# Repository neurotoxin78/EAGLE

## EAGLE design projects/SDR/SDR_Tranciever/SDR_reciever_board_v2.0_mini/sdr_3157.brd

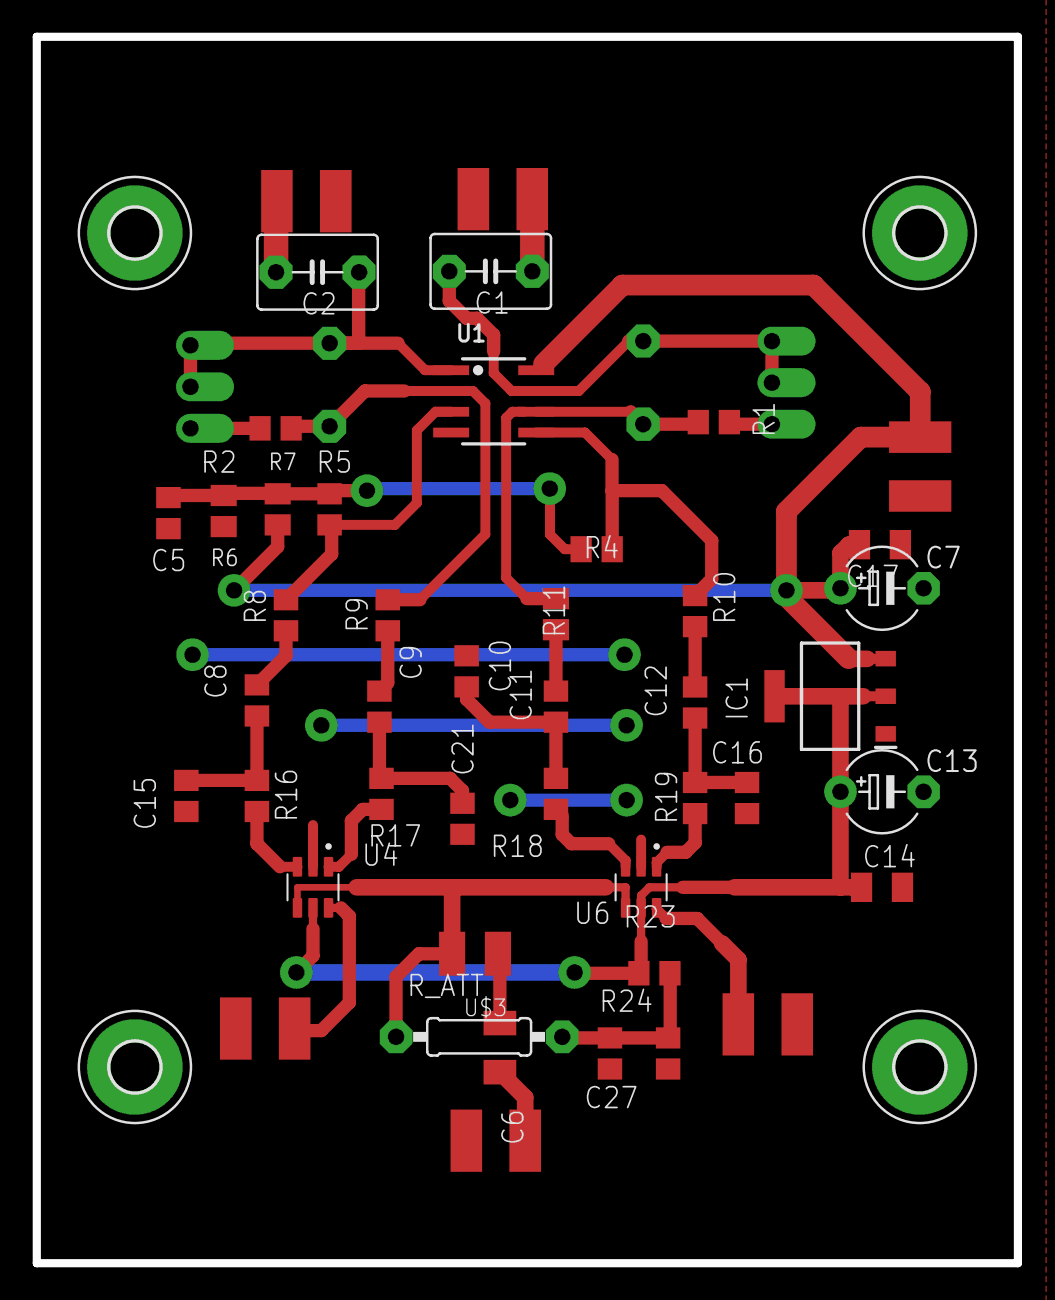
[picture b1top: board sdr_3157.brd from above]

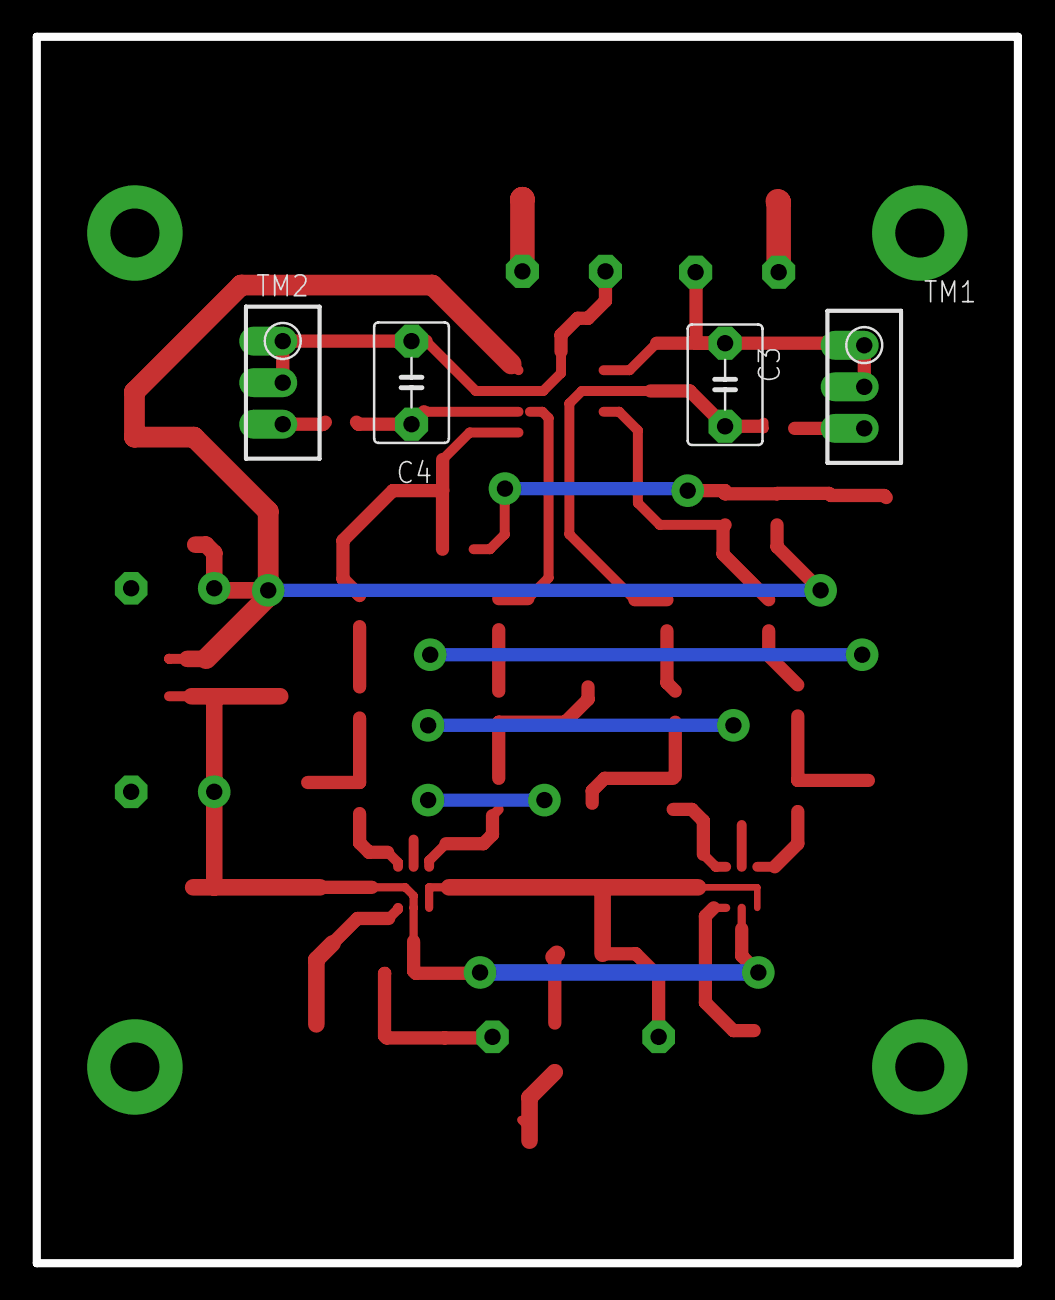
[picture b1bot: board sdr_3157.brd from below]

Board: 2 copper layers, 60.0 x 75.0 mm, 53 parts (4 on the bottom side), 32 nets.

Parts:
C1, C2: 1uF; C050-045X075
C3, C4: 200pF; C050-045X075
C5: 10uF; C0805
C6: 22nF; C1206K
C7, C13: E5-5
C8, C9, C11, C12, C27: 1uF; C0805
C10, C15, C16, C21: 22nF; C0805
C14, C17: C0805
COS: 2XSMD_PIN
H1, H2, H3, H4: MOUNT-PAD-ROUND3.0; 3,0-PAD
I: 2XSMD_PIN
IC1: LM1117-33; SOT230P700X180-4N
Q: 2XSMD_PIN
R1, R2: 7k5; R0805
R4: 10k; M0805
R5: 10k; R0805
R6, R7, R11: 1k; M0805
R8, R9, R10, R23, R24: 1k; R0805
R16, R17, R18, R19: 20; R0805
RF_IN, RF_IN1: 2XSMD_PIN
R_ATT: 20; R1210
SIN: 2XSMD_PIN
TM1, TM2: 5k; RTRIM3296W
U1: NE5532D; SO08
U4, U6: SN74LVC1G3157DBVR; SOT95P280X145-6N
U$3: 100uH; 0207/10

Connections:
12V: C7.+, C17.2, IC1.3, R7.1, RF_IN1.P$2, U1.8
ANTENNA: R_ATT.2, U4.4, U6.4, U$3.2
COS_IN: COS.P$2, U4.6
GND: C5.1, C7.-, C10.2, C13.-, C14.2, C15.2, C16.1, C17.1, C21.1, C27.1, COS.P$1, H1.B3,0, H2.B3,0, H3.B3,0, H4.B3,0, I.P$1, IC1.1, Q.P$2, R6.1, R23.1, RF_IN.P$1, RF_IN1.P$1, SIN.P$1, U1.4, U4.2, U6.2
unnamed: C6.2, RF_IN.P$2
unnamed: C6.1, R_ATT.1
unnamed: R16.1, U4.3
unnamed: R17.1, U4.1
unnamed: R18.1, U6.3
unnamed: R19.1, U6.1
unnamed: C8.1, C15.1, R16.2
unnamed: C9.1, C21.2, R17.2
unnamed: C10.1, C11.1, R18.2
unnamed: C12.1, C16.2, R19.2
unnamed: C8.2, R8.1
unnamed: C9.2, R9.1
unnamed: C11.2, R11.1
unnamed: C12.2, R10.1
unnamed: R5.2, R8.2, U1.3
unnamed: C3.1, R2.1, R9.2, U1.2
unnamed: R4.2, R10.2, U1.5
unnamed: C4.1, R1.1, R11.2, U1.6
unnamed: C5.2, R4.1, R5.1, R6.2, R7.2
unnamed: C2.1, C3.2, TM1.1, TM1.2, U1.1
unnamed: C2.2, Q.P$1
unnamed: C1.1, I.P$2
unnamed: C1.2, C4.2, TM2.1, TM2.2, U1.7
unnamed: C27.2, R23.2, R24.2, U$3.1
unnamed: R2.2, TM1.3
unnamed: R1.2, TM2.3
SIN_IN: SIN.P$2, U6.6
VCC: C13.+, C14.1, IC1.2, IC1.4, R24.1, U4.5, U6.5

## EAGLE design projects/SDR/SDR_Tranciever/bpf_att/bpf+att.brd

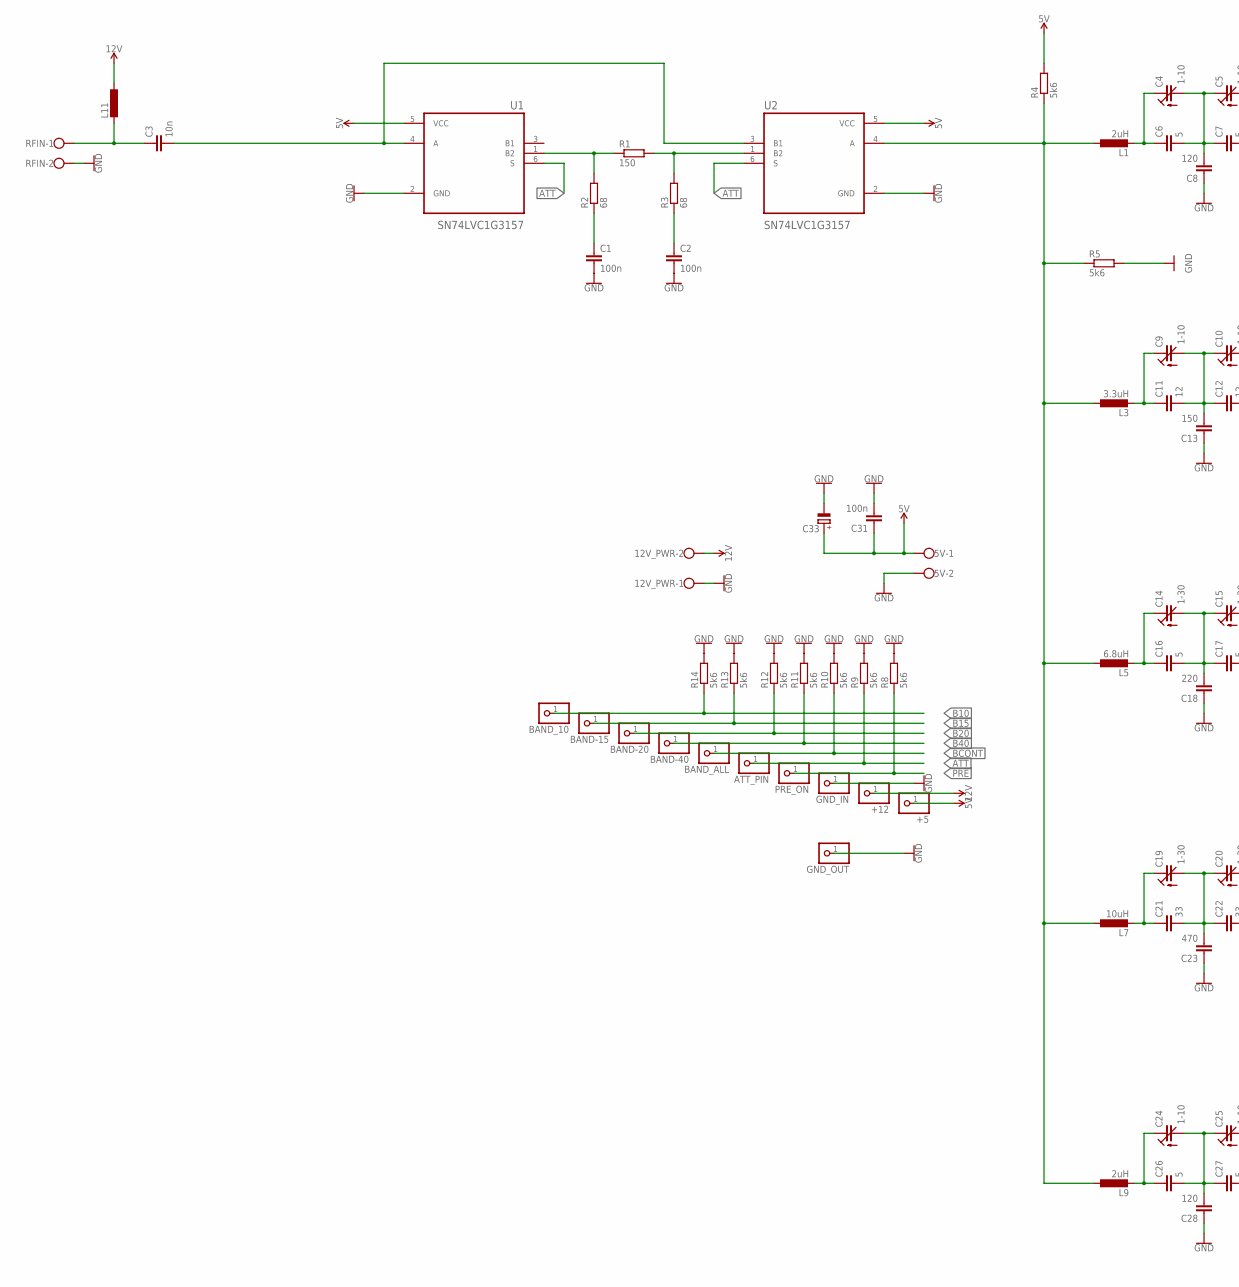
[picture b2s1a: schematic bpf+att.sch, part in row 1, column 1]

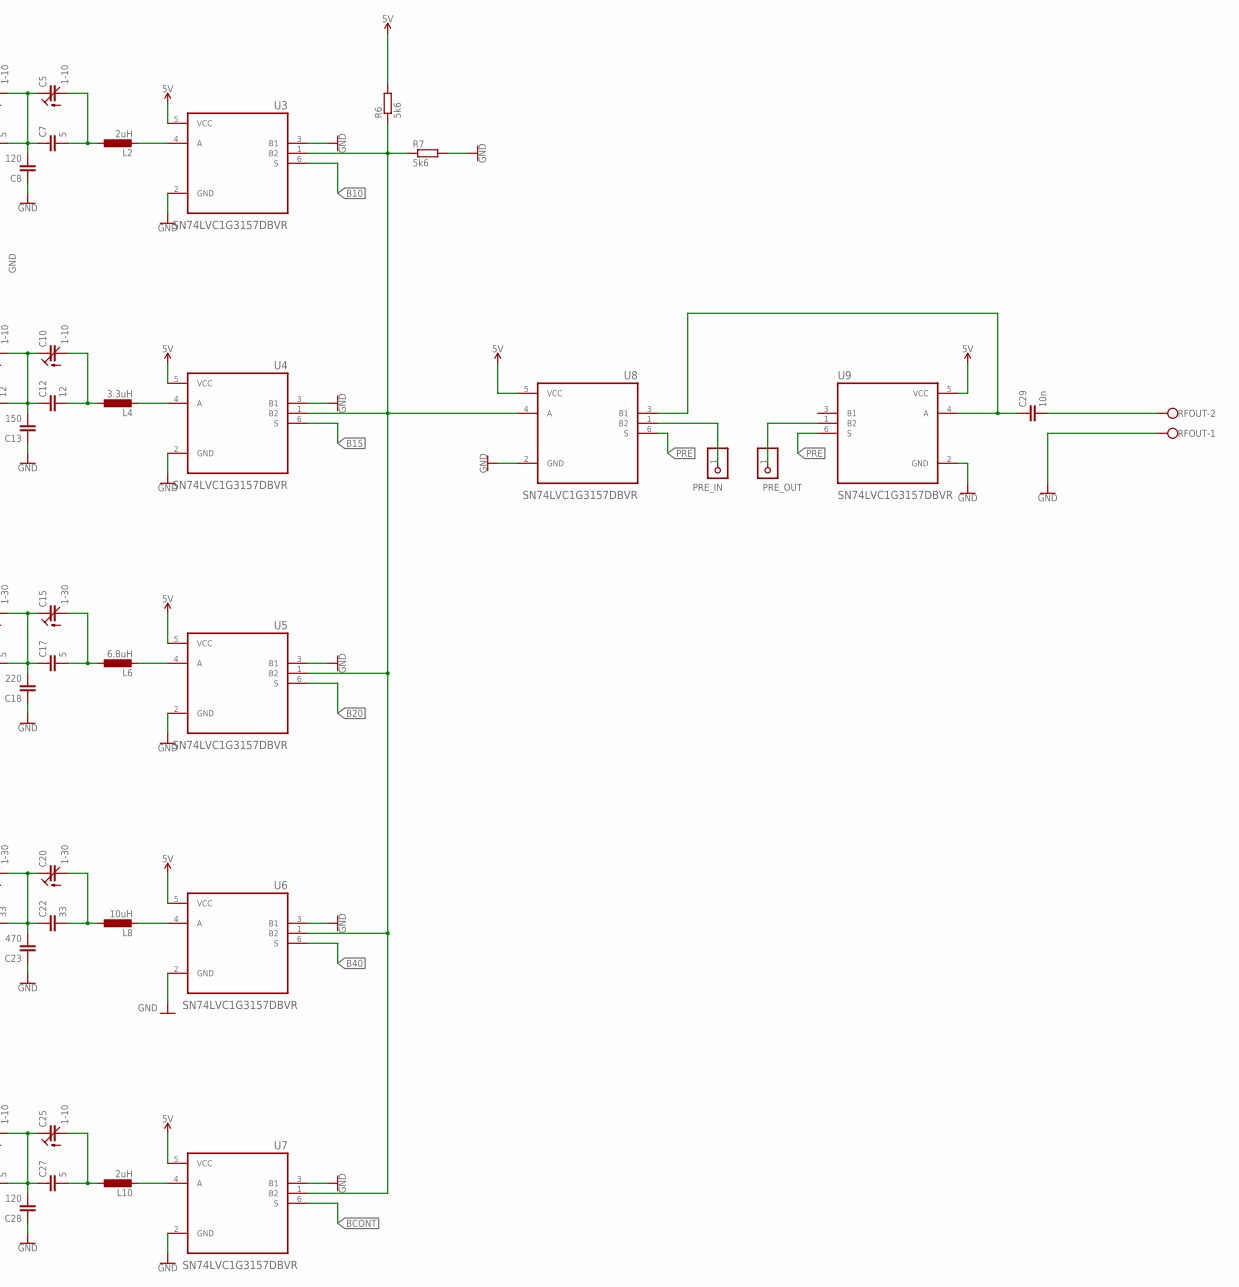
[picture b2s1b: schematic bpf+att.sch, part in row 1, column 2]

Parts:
5V, 12V_PWR: W237-102
+5, +12: PINHD-1X1; 1X01
ATT_PIN: PINHD-1X1; 1X01
BAND-15, BAND-20, BAND-40: PINHD-1X1; 1X01
BAND_10: PINHD-1X1; 1X01
BAND_ALL: PINHD-1X1; 1X01
C1, C2, C31: 100n; C1206
C3, C29: 10n; C1206K
C4, C5, C9, C10, C24, C25: 1-10; CTRIM3050.504
C6, C7, C16, C17, C26, C27: 5; C1206K
C8, C28: 120; C1206K
C11, C12: 12; C1206K
C13: 150; C1206K
C14, C15, C19, C20: 1-30; CTRIM3050.504
C18: 220; C1206K
C21, C22: 33; C1206K
C23: 470; C1206K
C33: CPOL-EUSMCD; SMC_D
GND_IN: PINHD-1X1; 1X01
GND_OUT: PINHD-1X1; 1X01
L1, L2, L9, L10: 2uH; 0204/7
L3, L4: 3.3uH; 0204/7
L5, L6: 6.8uH; 0204/7
L7, L8: 10uH; 0204/7
L11: L-EU0204/7; 0204/7
PRE_IN: PINHD-1X1; 1X01
PRE_ON: PINHD-1X1; 1X01
PRE_OUT: PINHD-1X1; 1X01
R1: 150; R1206
R2, R3: 68; R1206
R4, R5, R8, R9: 5k6; R1206
R6, R7, R10, R11, R12, R13, R14: 5k6; R0805
RFIN: W237-102
RFOUT: W237-102
U1, U2: SN74LVC1G3157; SOT95P280X145-6N
U3, U4, U5, U6, U7, U8, U9: SN74LVC1G3157DBVR; SOT95P280X145-6N

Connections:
5V: 5V.1, +5.1, C31.1, C33.+, R4.2, R6.2, U1.5 (VCC), U2.5 (VCC), U3.5 (VCC), U4.5 (VCC), U5.5 (VCC), U6.5 (VCC), U7.5 (VCC), U8.5 (VCC), U9.5 (VCC)
12V: 12V_PWR.2, +12.1, L11.1
ATT: ATT_PIN.1, R9.1, U1.6 (S), U2.6 (S)
B10: BAND_10.1, R14.1, U3.6 (S)
B15: BAND-15.1, R13.1, U4.6 (S)
B20: BAND-20.1, R12.1, U5.6 (S)
B40: BAND-40.1, R11.1, U6.6 (S)
BCONT: BAND_ALL.1, R10.1, U7.6 (S)
BYPASS: R6.1, R7.1, U3.1 (B2), U4.1 (B2), U5.1 (B2), U6.1 (B2), U7.1 (B2), U8.4 (A)
FILTER_INPUT: L1.1, L3.1, L5.1, L7.1, L9.1, R4.1, R5.1, U2.4 (A)
GND: 5V.2, 12V_PWR.1, C1.2, C2.2, C8.1, C13.1, C18.1, C23.1, C28.1, C31.2, C33.-, GND_IN.1, GND_OUT.1, R5.2, R7.2, R8.2, R9.2, R10.2, R11.2, R12.2, R13.2, R14.2, RFIN.2, RFOUT.1, U1.2 (GND), U2.2 (GND), U3.2 (GND), U3.3 (B1), U4.2 (GND), U4.3 (B1), U5.2 (GND), U5.3 (B1), U6.2 (GND), U6.3 (B1), U7.2 (GND), U7.3 (B1), U8.2 (GND), U9.2 (GND)
unnamed: R1.1, R2.2, U1.1 (B2)
unnamed: R1.2, R3.2, U2.1 (B2)
unnamed: C1.1, R2.1
unnamed: C2.1, R3.1
unnamed: C3.2, U1.4 (A), U2.3 (B1)
unnamed: C3.1, L11.2, RFIN.1
unnamed: C4.1 (E), C6.1, L1.2
unnamed: C4.2 (A), C5.1 (E), C6.2, C7.1, C8.2
unnamed: C5.2 (A), C7.2, L2.1
unnamed: L2.2, U3.4 (A)
unnamed: C29.1, U8.3 (B1), U9.4 (A)
unnamed: C9.1 (E), C11.1, L3.2
unnamed: C9.2 (A), C10.1 (E), C11.2, C12.1, C13.2
unnamed: C10.2 (A), C12.2, L4.1
unnamed: L4.2, U4.4 (A)
unnamed: C29.2, RFOUT.2
unnamed: PRE_IN.1, U8.1 (B2)
unnamed: C14.1 (E), C16.1, L5.2
unnamed: C14.2 (A), C15.1 (E), C16.2, C17.1, C18.2
unnamed: C15.2 (A), C17.2, L6.1
unnamed: L6.2, U5.4 (A)
unnamed: PRE_OUT.1, U9.1 (B2)
unnamed: C19.1 (E), C21.1, L7.2
unnamed: C19.2 (A), C20.1 (E), C21.2, C22.1, C23.2
unnamed: C20.2 (A), C22.2, L8.1
unnamed: L8.2, U6.4 (A)
unnamed: C24.1 (E), C26.1, L9.2
unnamed: C24.2 (A), C25.1 (E), C26.2, C27.1, C28.2
unnamed: C25.2 (A), C27.2, L10.1
unnamed: L10.2, U7.4 (A)
PRE: PRE_ON.1, R8.1, U8.6 (S), U9.6 (S)

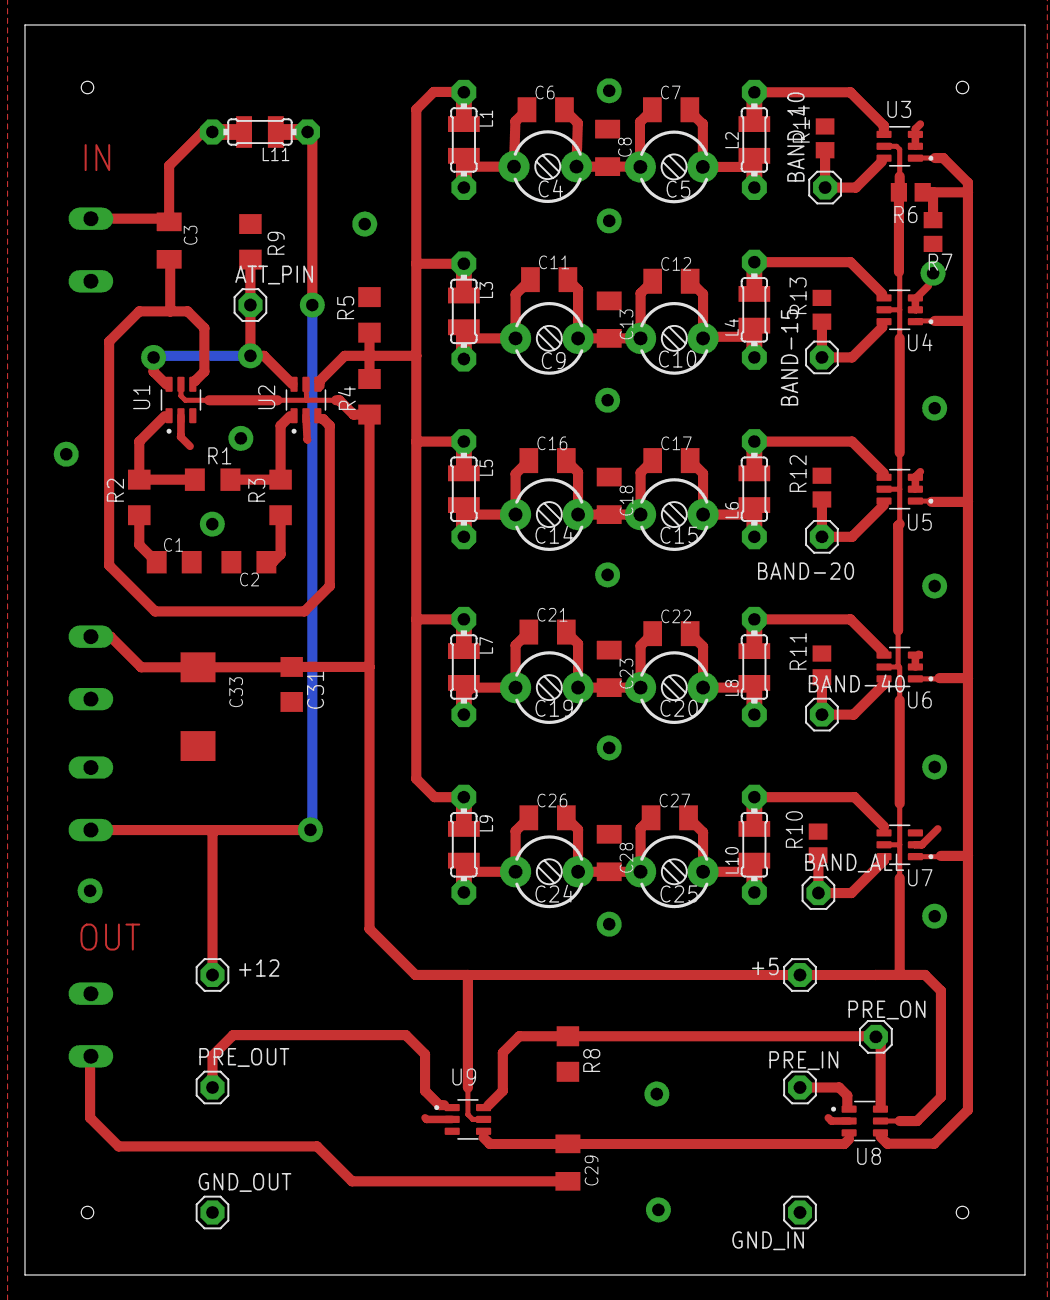
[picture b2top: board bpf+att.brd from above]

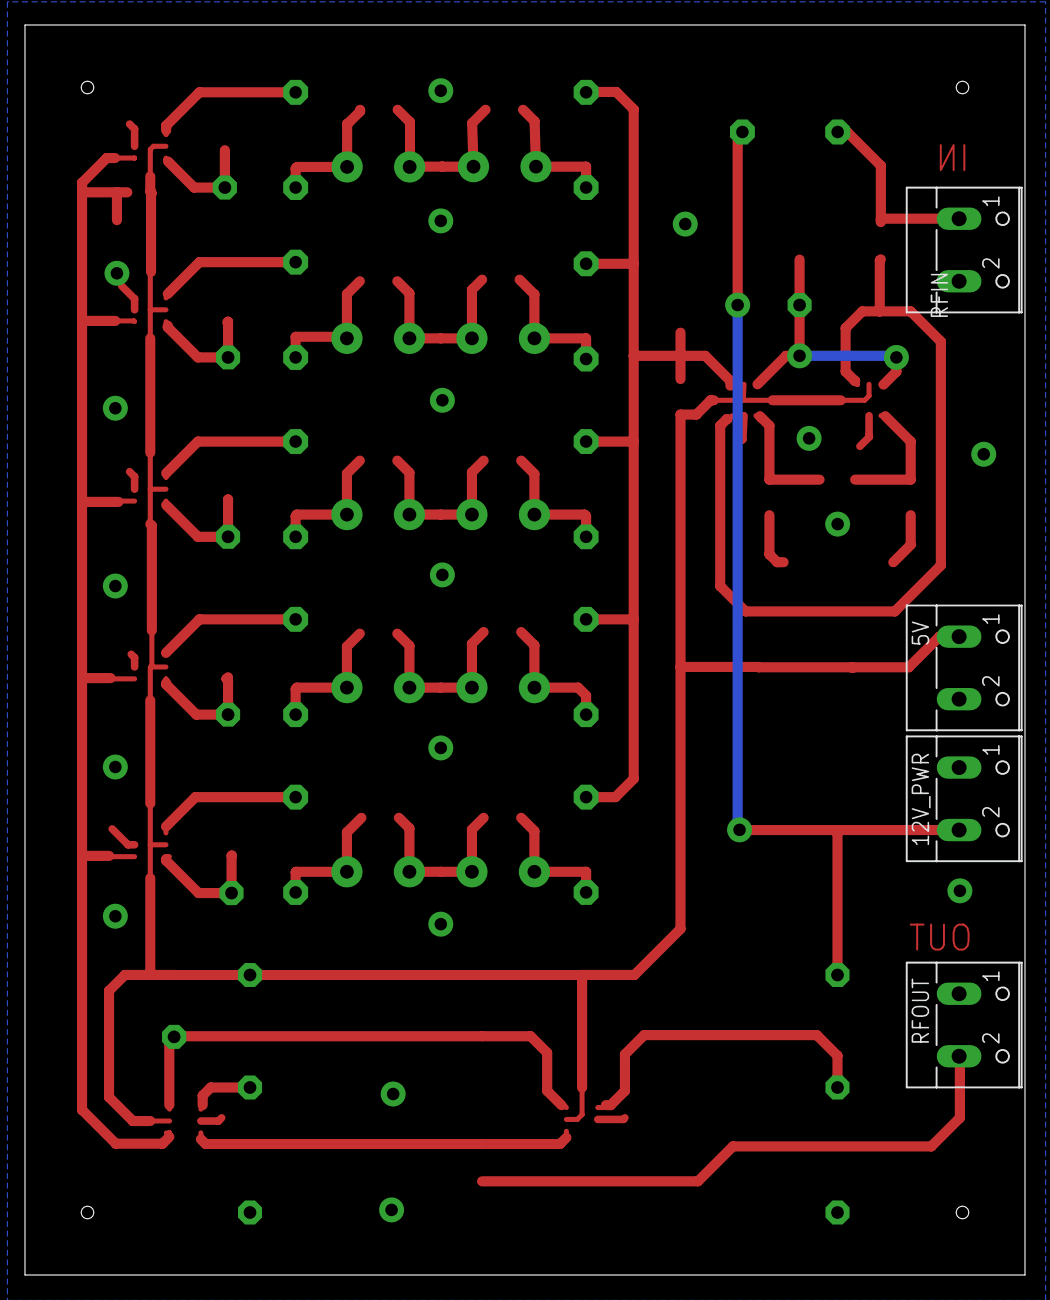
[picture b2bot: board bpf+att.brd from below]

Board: 2 copper layers, 80.0 x 100.0 mm, 82 parts (4 on the bottom side), 42 nets.

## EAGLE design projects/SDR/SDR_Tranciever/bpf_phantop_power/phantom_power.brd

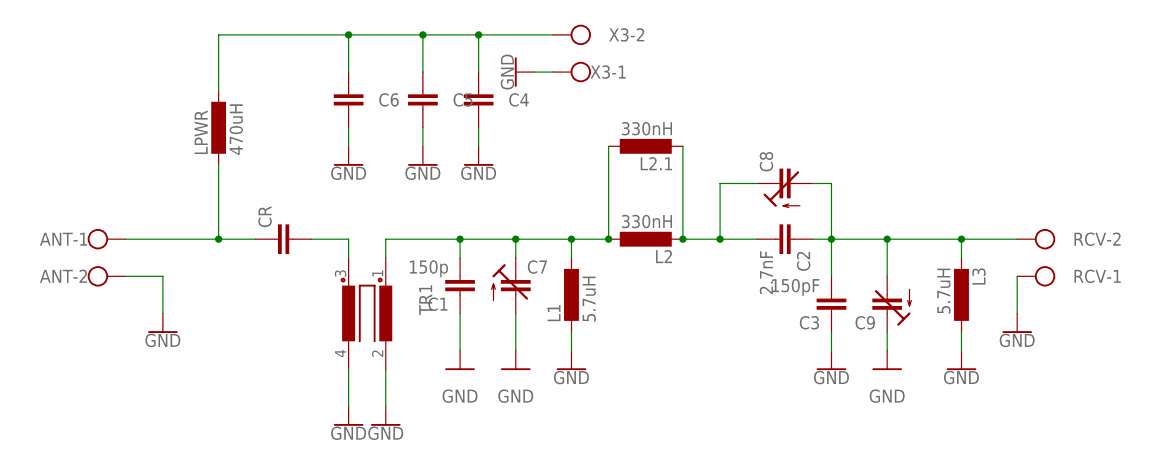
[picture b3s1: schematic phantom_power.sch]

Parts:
ANT: W237-102
C1: 150p; C1206K
C2: 2.7nF; C1206K
C3: 150pF; C1206K
C4, C5, C6: C-EUC1206K; C1206K
C7, C8, C9: C-TRIMM3050.504; CTRIM3050.504
CR: C-EUC1206K; C1206K
L1, L3: 5.7uH; 0204/7
L2: 330nH; L1812
L2.1: 330nH; 0204/7
LPWR: 470uH; 0204/7
RCV: W237-102
TR1: R1405UB1/2; B1/2
X3: W237-102

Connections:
GND: ANT.2, C1.1, C3.1, C4.2, C5.2, C6.2, C7.2 (A), C9.1 (E), L1.2, L3.1, RCV.1, TR1.2, TR1.4, X3.1
unnamed: ANT.1, CR.1, LPWR.2
unnamed: C4.1, C5.1, C6.1, LPWR.1, X3.2
unnamed: C2.1, C3.2, C8.2 (A), C9.2 (A), L3.2, RCV.2
unnamed: C1.2, C7.1 (E), L1.1, L2.1, L2.1.1, TR1.1
unnamed: C2.2, C8.1 (E), L2.2, L2.1.2
unnamed: CR.2, TR1.3

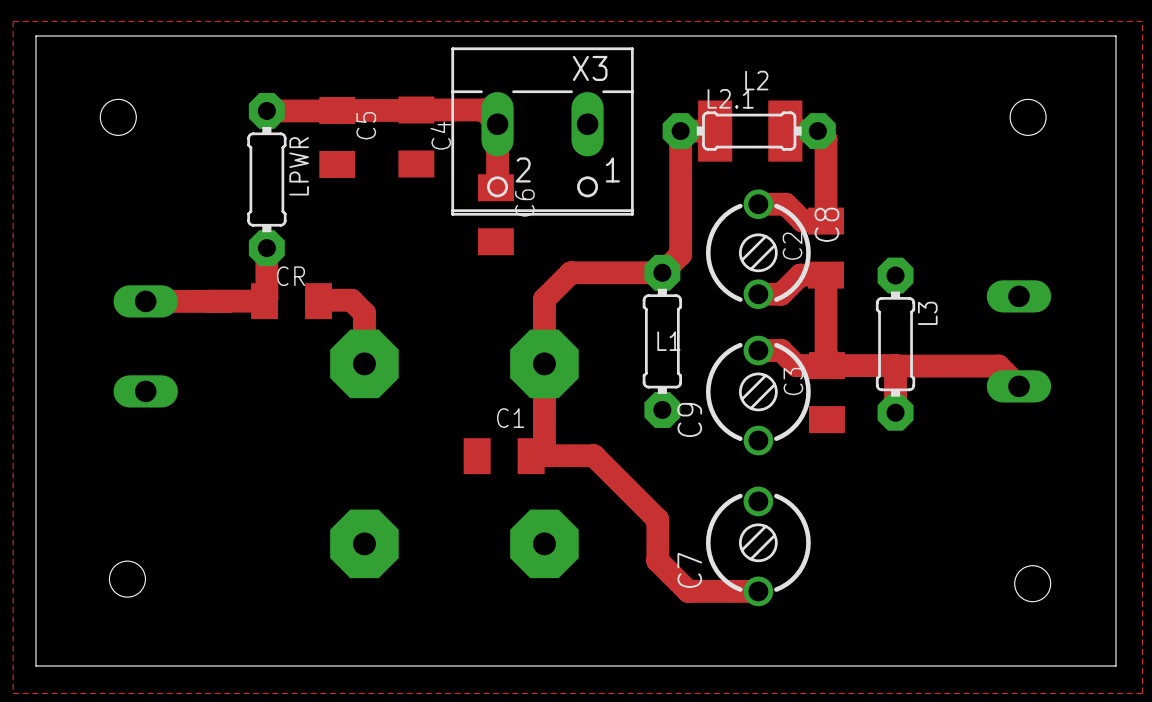
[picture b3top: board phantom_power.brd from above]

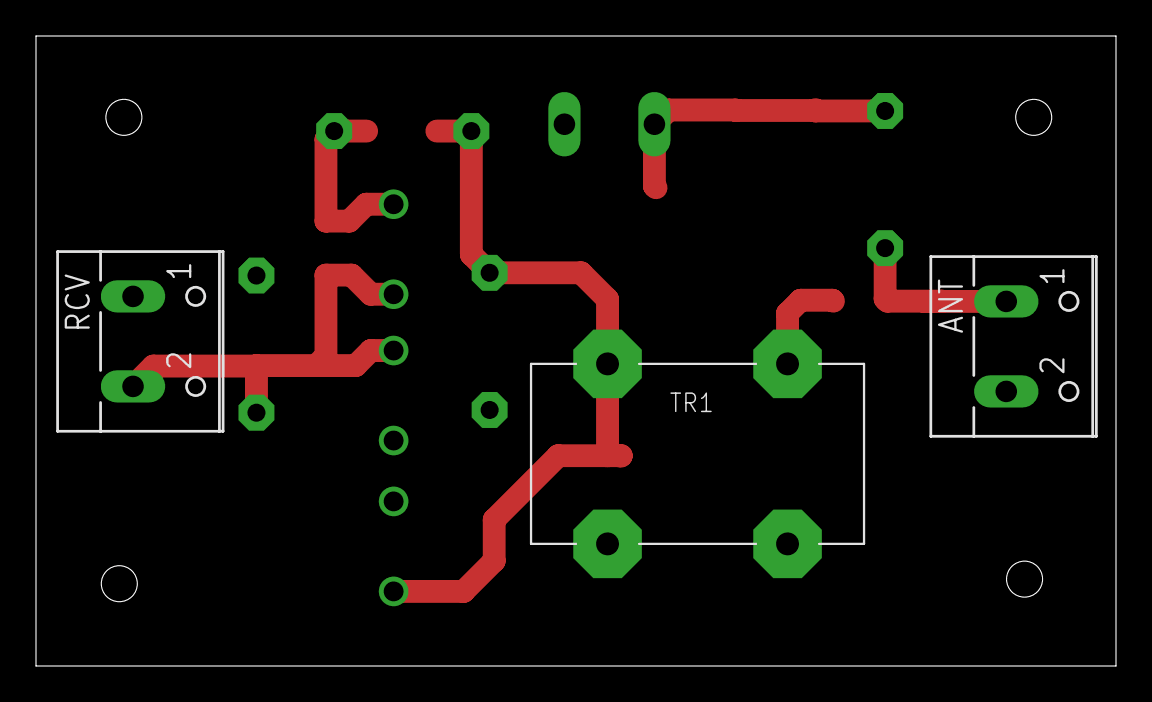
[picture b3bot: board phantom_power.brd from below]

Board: 2 copper layers, 60.0 x 35.0 mm, 19 parts (3 on the bottom side), 7 nets.

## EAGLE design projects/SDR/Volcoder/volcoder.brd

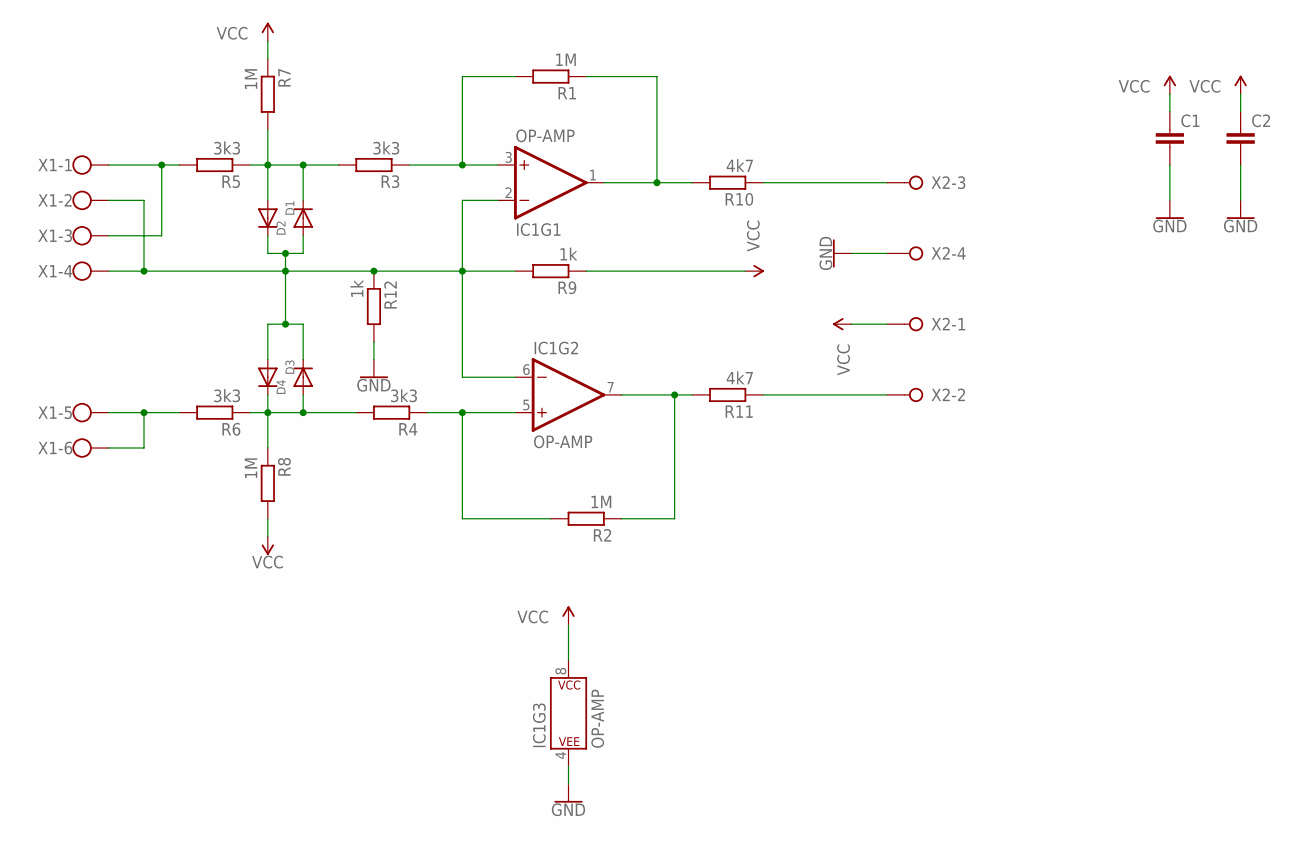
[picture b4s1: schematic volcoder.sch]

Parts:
C1, C2: C-EUC0805; C0805
D1, D2, D3, D4: DIODE_SOD-123FL; SOD-123FL
IC1: OP-AMP; SO08
R1, R2, R7: 1M; R0805
R3, R4, R5, R6: 3k3; R0805
R8: 1M; M0805
R9: 1k; R0805
R10, R11: 4k7; R0805
R12: 1k; M0805
X1: W237-136
X2: W237-04P; W237-4P

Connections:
GND: C1.2, C2.2, IC1.4 (P$V-), R12.2, X2.4
unnamed: IC1.5 (+IN), R2.2, R4.1
unnamed: IC1.7 (OUT), R2.1, R11.2
unnamed: IC1.1 (OUT), R1.1, R10.2
unnamed: IC1.3 (+IN), R1.2, R3.1
unnamed: R11.1, X2.2
unnamed: D1.A, D2.C, R3.2, R5.1, R7.2
unnamed: D3.C, D4.A, R4.2, R6.1, R8.1
unnamed: R5.2, X1.1, X1.3
unnamed: R6.2, X1.5, X1.6
unnamed: D1.C, D2.A, D3.A, D4.C, IC1.2 (-IN), IC1.6 (-IN), R9.2, R12.1, X1.2, X1.4
unnamed: R10.1, X2.3
VCC: C1.1, C2.1, IC1.8 (P$V+), R7.1, R8.2, R9.1, X2.1

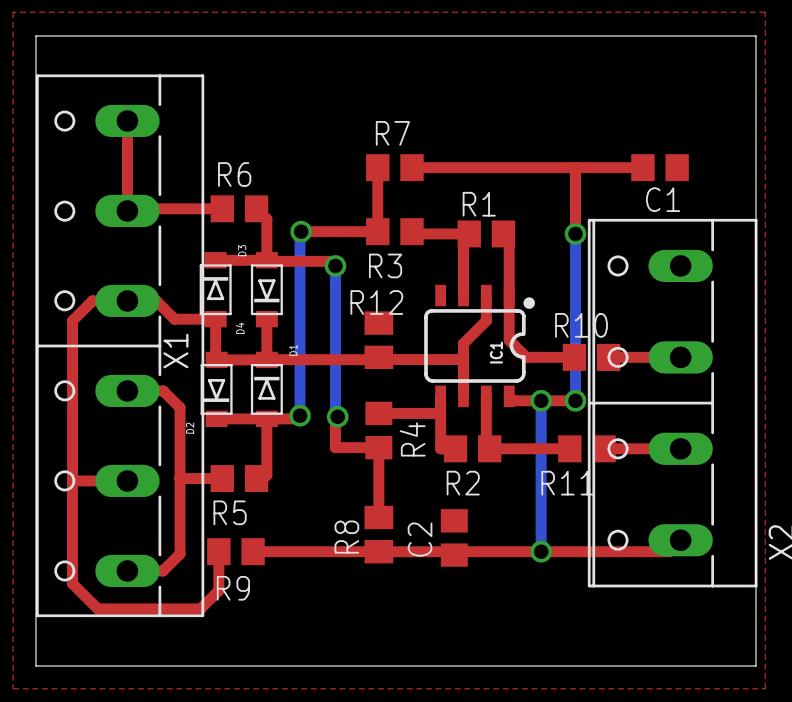
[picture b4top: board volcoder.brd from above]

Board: 2 copper layers, 40.0 x 35.0 mm, 21 parts (0 on the bottom side), 13 nets.

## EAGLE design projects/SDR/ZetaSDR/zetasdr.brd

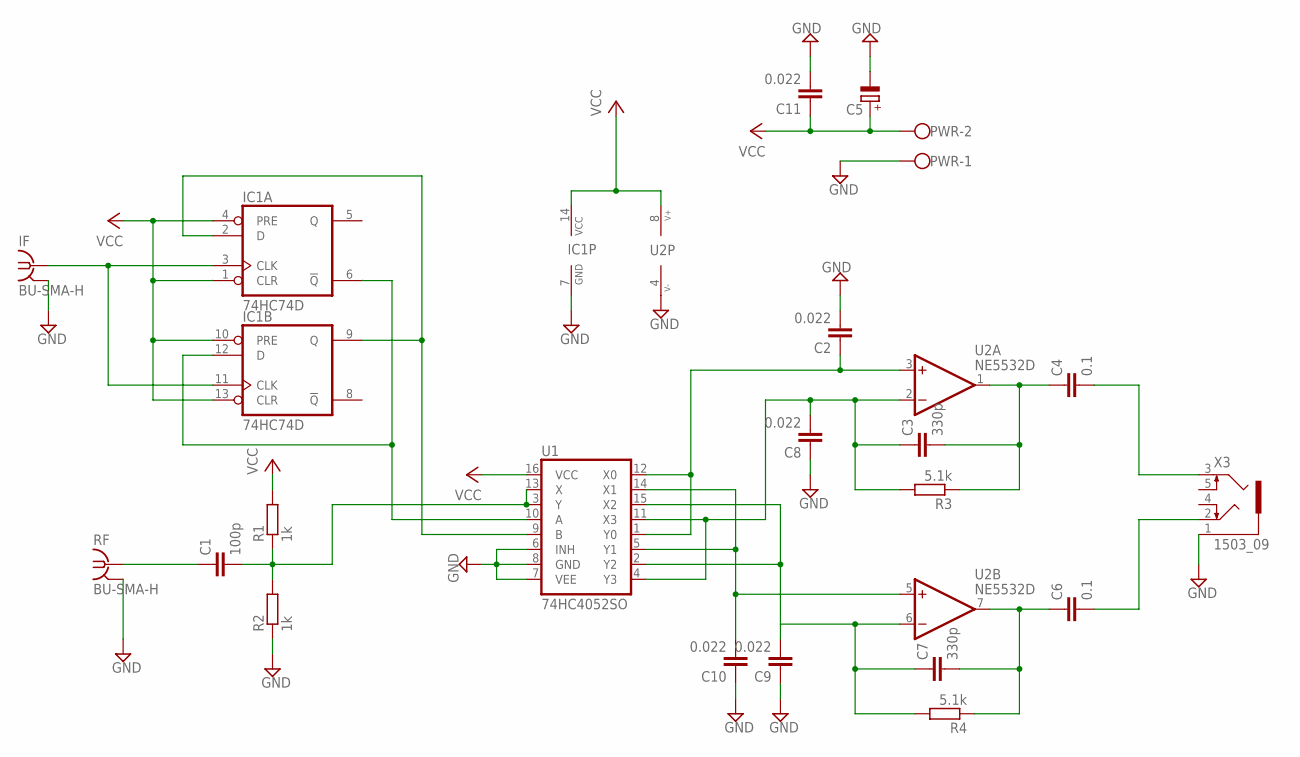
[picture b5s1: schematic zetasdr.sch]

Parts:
C1: 100p; C0805
C2, C8, C9, C10, C11: 0.022; C0805
C3, C7: 330p; C0805
C4, C6: 0.1; C050-045X075
C5: CPOL-EUE3.5-8; E3,5-8
IC1: 74HC74D; SO14
IF: BU-SMA-H
PWR: W237-102
R1, R2: 1k; M0805
R3, R4: 5.1k; R0805
RF: BU-SMA-H
U1: 74HC4052SO; SO16
U2: NE5532D; SO08
X3: 1503_09

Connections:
GND: C2.2, C5.-, C8.1, C9.1, C10.1, C11.2, IC1.7 (GND), IF.2, IF.3 (2), IF.4 (2), IF.5 (2), PWR.1, R2.1, RF.2, RF.3 (2), RF.4 (2), RF.5 (2), U1.6 (INH), U1.7 (VEE), U1.8 (GND), U2.4 (V-), X3.1
unnamed: IC1.3 (CLK), IC1.11 (CLK), IF.1
unnamed: IC1.6 (!Q), IC1.12 (D), U1.10 (A)
unnamed: IC1.2 (D), IC1.9 (Q), U1.9 (B)
unnamed: C1.1, RF.1
unnamed: C1.2, R1.1, R2.2, U1.3 (Y), U1.13 (X)
unnamed: C2.1, U1.1 (Y0), U1.12 (X0), U2.3 (+IN)
unnamed: C3.2, C4.1, R3.1, U2.1 (OUT)
unnamed: C3.1, C8.2, R3.2, U1.4 (Y3), U1.11 (X3), U2.2 (-IN)
unnamed: C4.2, X3.3
unnamed: C10.2, U1.5 (Y1), U1.14 (X1), U2.5 (+IN)
unnamed: C6.1, C7.2, R4.1, U2.7 (OUT)
unnamed: C6.2, X3.2
unnamed: C7.1, C9.2, R4.2, U1.2 (Y2), U1.15 (X2), U2.6 (-IN)
VCC: C5.+, C11.1, IC1.1 (CLR), IC1.4 (PRE), IC1.10 (PRE), IC1.13 (CLR), IC1.14 (VCC), PWR.2, R1.2, U1.16 (VCC), U2.8 (V+)

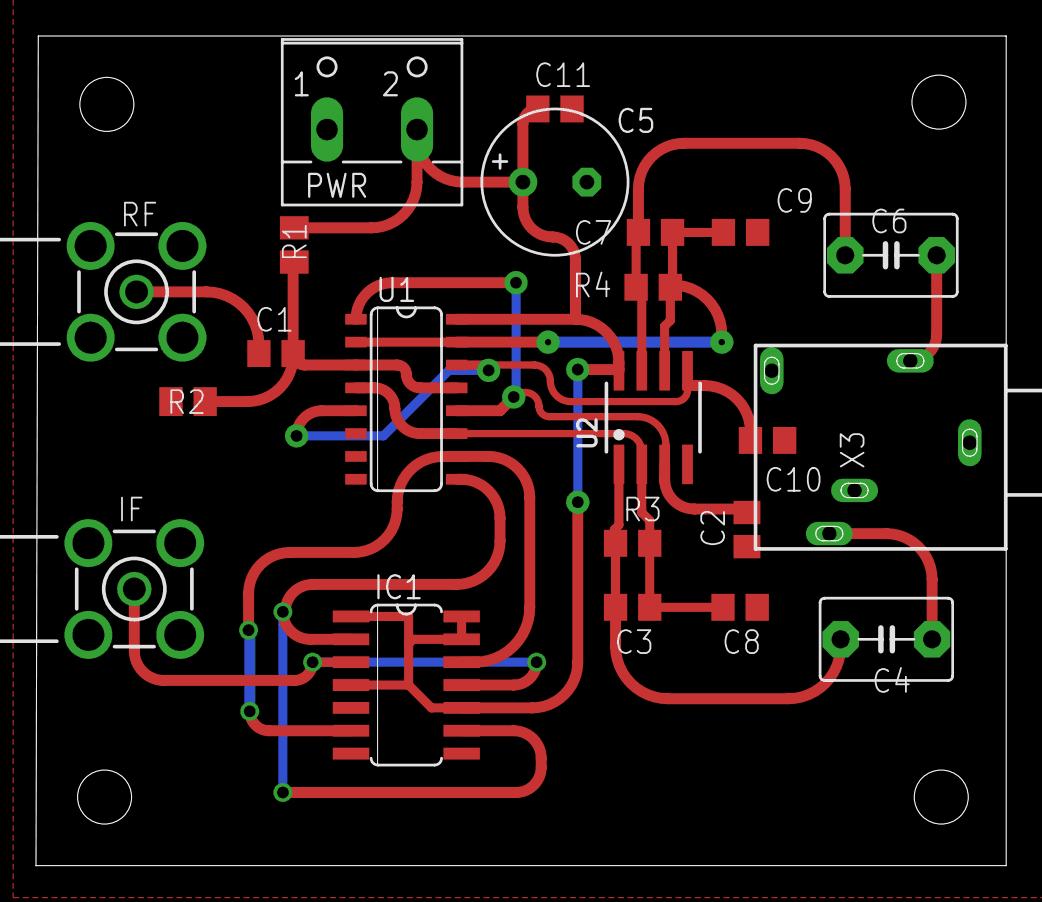
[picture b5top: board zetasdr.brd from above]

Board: 2 copper layers, 53.9 x 46.1 mm, 22 parts (0 on the bottom side), 15 nets.

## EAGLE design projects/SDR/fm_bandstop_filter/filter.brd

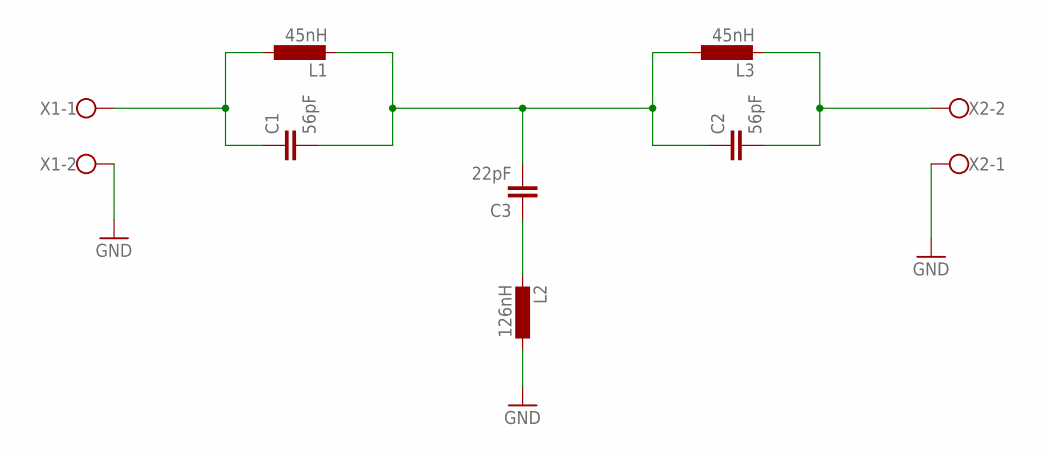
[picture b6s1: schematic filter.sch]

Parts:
C1, C2: 56pF; C0805K
C3: 22pF; C0805K
L1, L3: 45nH; 0204/7
L2: 126nH; 0207/10
X1, X2: W237-102

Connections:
GND: L2.1, X1.2, X2.1
unnamed: C1.1, L1.1, X1.1
unnamed: C1.2, C2.1, C3.2, L1.2, L3.1
unnamed: C2.2, L3.2, X2.2
unnamed: C3.1, L2.2

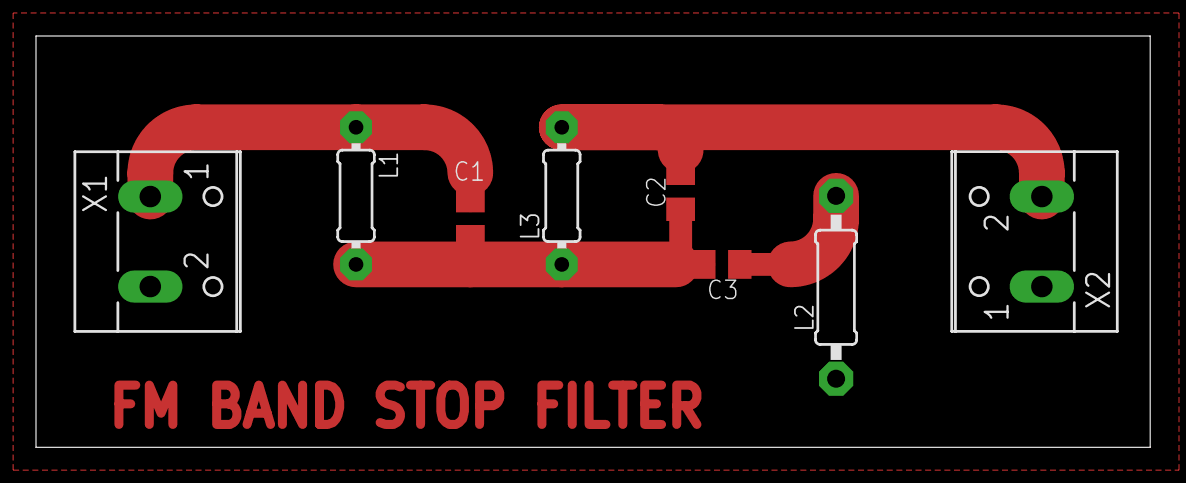
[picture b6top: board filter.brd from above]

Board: 2 copper layers, 61.9 x 22.9 mm, 8 parts (0 on the bottom side), 5 nets.

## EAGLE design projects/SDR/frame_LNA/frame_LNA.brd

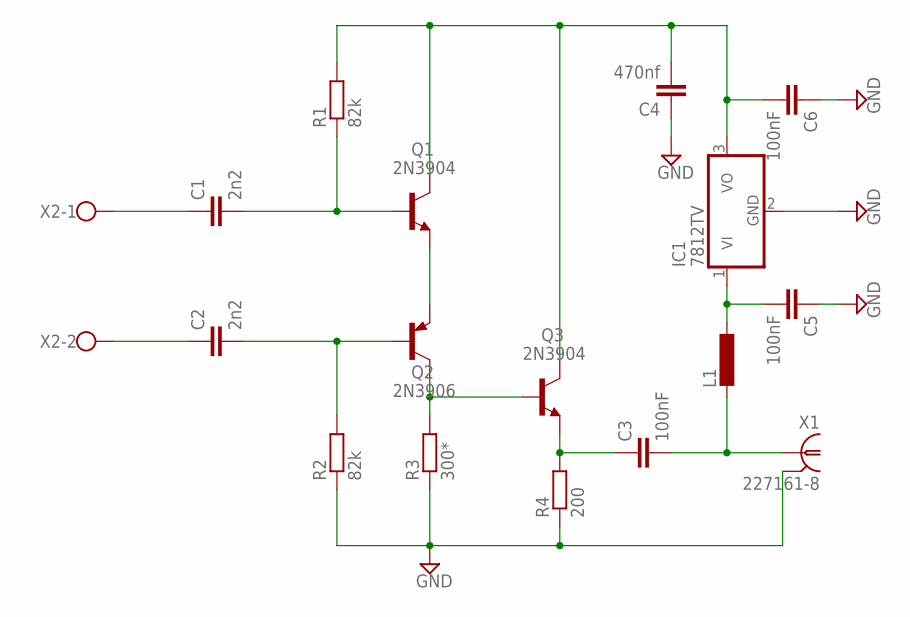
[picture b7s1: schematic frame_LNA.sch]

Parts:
C1, C2: 2n2; C0805K
C3, C5, C6: 100nF; C0805K
C4: 470nf; C0805K
IC1: 7812TV; TO220V
L1: L-EU0207/12; 0207/12
Q1, Q3: 2N3904; TO92
Q2: 2N3906; TO92
R1, R2: 82k; R0805
R3: 300*; R0805
R4: 200; R0805
X1: 227161-8; AMP_227161
X2: W237-102

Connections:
GND: C4.1, C5.1, C6.1, IC1.2 (GND), R2.1, R3.1, R4.1, X1.2
unnamed: Q1.3 (E), Q2.3 (E)
unnamed: C1.2, Q1.2 (B), R1.1
unnamed: C2.2, Q2.2 (B), R2.2
unnamed: C4.2, C6.2, IC1.3 (VO), Q1.1 (C), Q3.1 (C), R1.2
unnamed: Q2.1 (C), Q3.2 (B), R3.2
unnamed: C3.1, Q3.3 (E), R4.2
unnamed: C3.2, L1.2, X1.1
unnamed: C1.1, X2.1
unnamed: C2.1, X2.2
unnamed: C5.2, IC1.1 (VI), L1.1

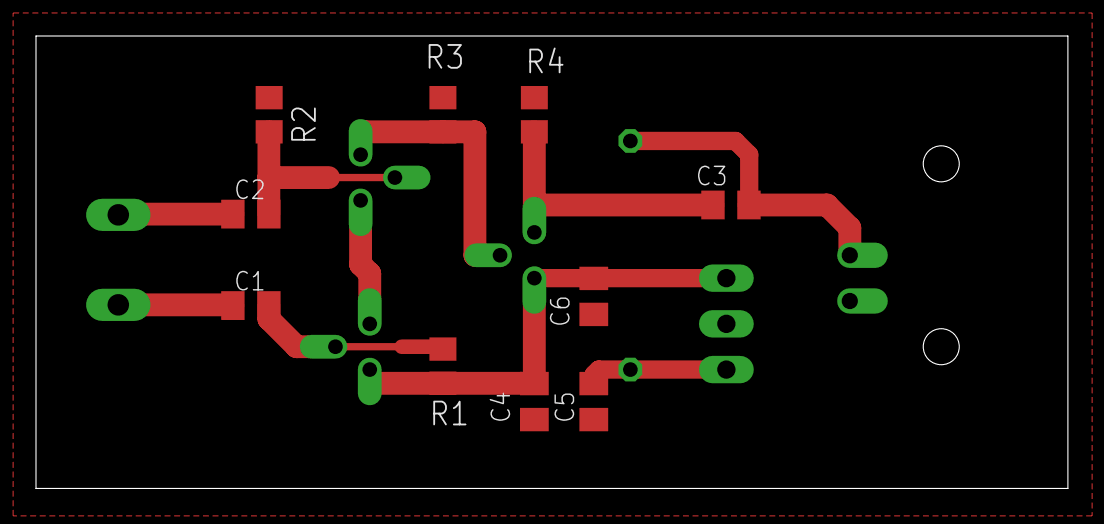
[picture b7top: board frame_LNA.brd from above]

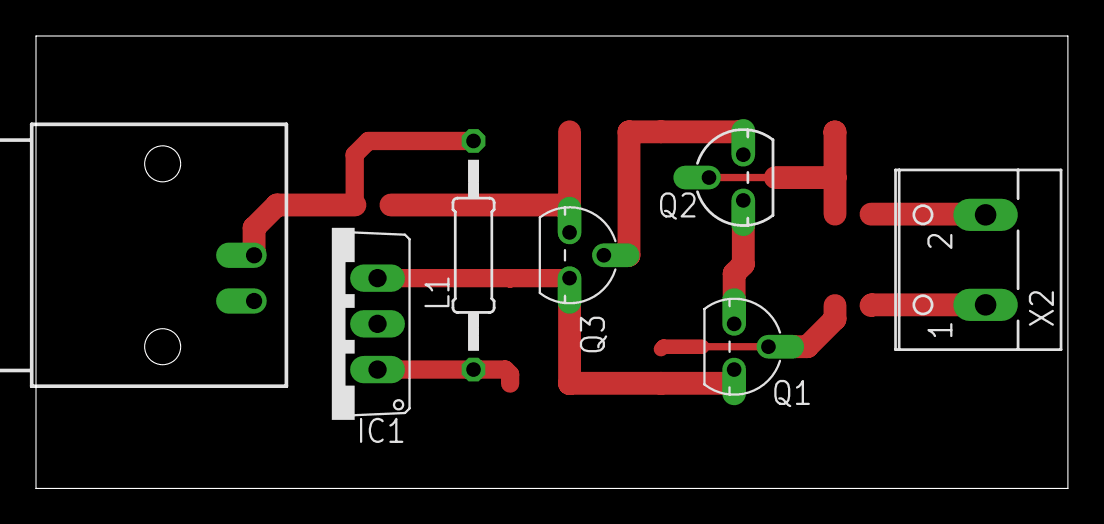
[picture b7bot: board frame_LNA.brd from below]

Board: 2 copper layers, 57.3 x 25.1 mm, 17 parts (7 on the bottom side), 11 nets.

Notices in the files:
parts and their libraries:
op-amp: Copyright (C) 2006 by Bob Starr
SparkFun-PowerSymbols: Licensing: Creative Commons ShareAlike 4.0 International - https://creativecommons.org/licenses/by-sa/4.0
